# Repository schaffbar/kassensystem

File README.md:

# Kassensystem

## Projektbeschreibung

Dies ist die Geschichte für die Entwicklung eines Abrechnungssystems für die SchaffBar,
einer offenen Werkstatt. Es sollen die Anwesenheiten der Besucher als die Nutzungszeiten
für ausgewählte elektrische Geräte zu Abrechnungszwecken erfasst werden.

Mittels eines RFID-Tags, das dem Besucher ausgehändigt wird, bei der Registrierung an der Theke,
wird beim Betreten und Verlassen des Werkstattbereichs ein Zeitpaar bestimmt,
das zur Abrechnung im Kassensystem herangezogen wird.
An einem Gerät kann mittels des RFID-Tags und einem WLan-Relais die Versorgungsspannung
eines Gerätes ein und ausgeschlatet werden und damit ebenfalls ein weiteres Zeitpaar
erstellt werden, das zur Abrechnung verwendet werden kann.

Das Lesen der RFID-Tags kann mittels eines RFID-Lesers erfolgen,
während die Daten in einer Datenbank auf einem Server gespeichert werden.

Daraus ergibt sich für das System folgende Aufteilung
- rfidReader - Bereitstellung des RFID-Tags an unterschiedlichen Positionen
- Comm Edge Device (TimeMachine) - Software auf dem Server dient als Schnittstelle zum Datenbanksystem
- ein Kassensystem

Als Kassensystem wird aktuell mit einer Offline Version von Odoo gearbeitet,
diese läuft in einem Docker-Container, in einem weiteren Container befindet sich die Datenbank,
ein weiteren Container wird es für die TimeMachine-Software geben.

## rfidReader

An folgenden oben beschriebenen Position kann ein RFID-Reader zur Anwendung kommen.
- dem Tresen
- dem Eingangsbereich zur Werkstatt
- an einem elektrischem Gerät "Gerätekontrolle"
diese Anwendungsfälle werden im weiteren Verlauf auch UseCases genannt.

Aktuell wird die ArduinoIDE zur Entwicklung verwendet, um aber die verwendeten Bibliotheken mitzuliefern
soll die Entwicklung auf PlatformIO umgestellt werden.
Auch soll die LVGL Bibliothek zukünftig verwendet werden, damit später das Handling von Schaltflächen und
anderem leichter implementiert werden kann.

### Hardwarebeschreibung

Eine Mikroprozessorsystem soll folgende Hardwaremerkmale aufweisen.
- ein Mikroprozessor mit einer WLan-Schnittstelle zur Kommunikation mit dem Server und den Datenbanken,
- einem RFID-Modul zum Lesen der ID-Nummer
- ein Display zur Darstellung von Informationen an den Benutzer,
   beziehungsweise Interaktion über die Touch-Funktionalität.

### Softwarebeschreibung

### Konfigurationsdaten

Um den Konfigurationsaufwand gering zuhalten wird beim Start des RFID-Readers die MAC-Adresse an den Server gesendet,
und anhand der Einträge in der Datenbank werden die Konfigurationsdaten an den RFID-Reader übertragen.

#### Tresen

Nach dem Auflegen des RFID-Tags auf dem RFID-Reader wird diese an den Server übertragen und in einer Datensatz der Datenbank abgelegt und steht zur weiteren Verarbeitung am Tresen zur Verfügung, wie Bearbeitung der Besucherdaten, zur Abrechnung, oder ...
Am Tresen erfolgt die Zuordnung des RFID-Tags zu einem Besucher

#### Eingangsbereich

Durch die Registrierung des Besuchers an der Theke hat dieser einen RFID-Tag erhalten, im Anschluss kann er seine Sachen richten, die er mit in den Werkstattbereich nehmen möchte. Beim Betreten und Verlassen des Werkstattbereichs hält der Besucher sein RFID-Tag an den RFID-Leser zur Erstellung einer Zeitmarke, die Differenz der Zeitspanne entspricht der Nutzungsdauer zur Abrechung. In Abhängigkeit der vorhandenen Datenbankeinträge ergibt sich das Betreten bzw. Verlassen der Werkstatt. Zur Berücksichtigung von Pausen oder ähnlichem können in der Datenbank mehrere Zeitpaare
eines Besuchers angelegt werden.

#### Gerätekontrolle

In den Stammdaten eines Besuchers ist hinterlegt, ob für einen Kunden die jeweilige Unterweisung für das Gerät erfolgt ist,
damit kann die unberechtige Verwendung von Geräten verhindert und die Unfallgefahr reduziert werden.
Nur wenn die Unterweisung hinterlegt ist, darf die Versorgungsspannung eingeschaltet werden, auch hier erfolgt die Abfrage
über die die Software auf dem Server.

## Comm Edge Device --Namensfindung

Diese Software bildet das Bindeglied zwischen den RFID-Reader und der Datenbank,
in Abhängigkeit des UseCases und dem Ergebnis der Datenbankabfrage wird die entsprechende Ausgabe auf dem RFID-Reader gessteuert.

## Kassensystem-SW

Aktuell soll eine offline Version von Odoo als Kassensystem verwendet werden,
da hier viele Funktionen bereits vorhanden sind.
Die Kopplung der RFID-Reader an das Kassensystem sowie die Auswertung der zusätzlichen Informationen
aus den hinzugefügten Tabellen muss noch erfolgen.

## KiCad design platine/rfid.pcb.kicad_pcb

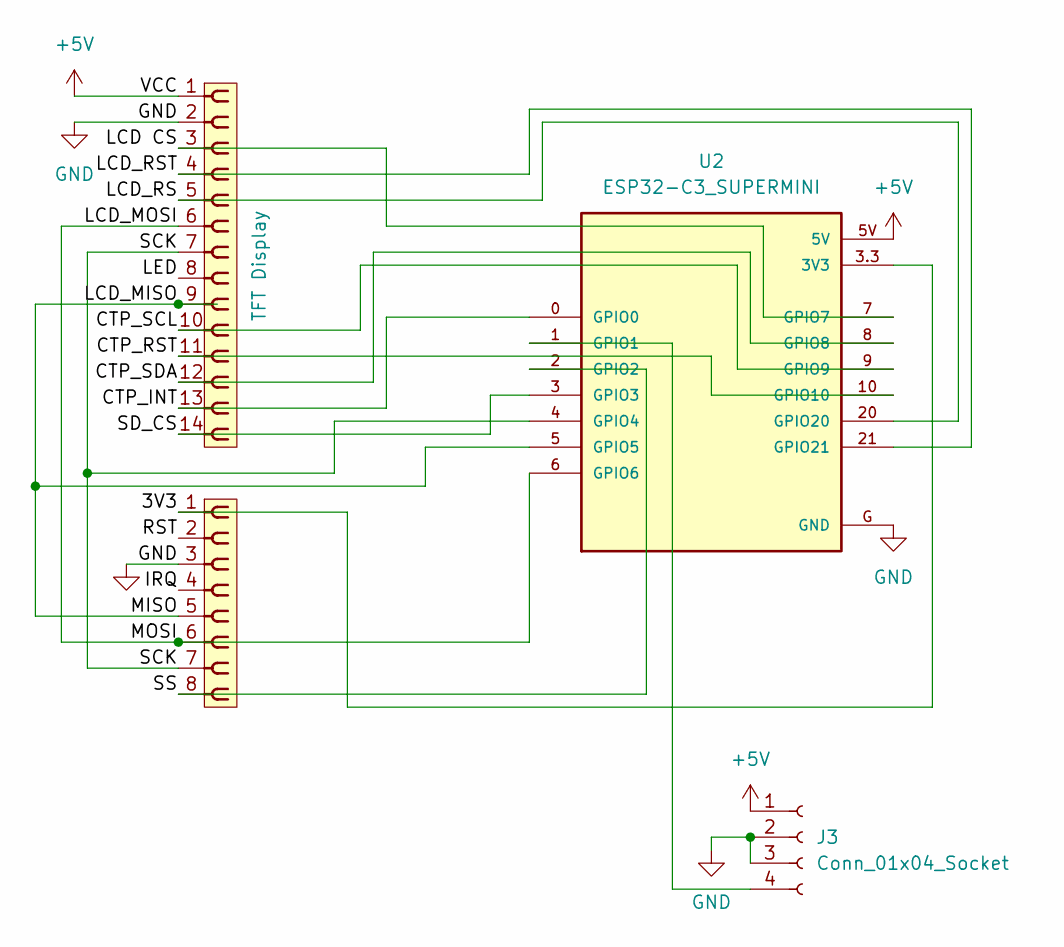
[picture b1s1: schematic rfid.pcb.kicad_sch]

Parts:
J1: TFT Display; PinSocket_1x14_P2.54mm_Vertical
J2: RFID Reader; PinSocket_1x08_P2.54mm_Vertical
J3: Conn_01x04_Socket; PinSocket_1x04_P2.54mm_Vertical
U2: ESP32-C3_SUPERMINI; MODULE_ESP32-C3_SUPERMINI

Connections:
+5V: J1.1, J3.1, U2.5V
/3V3: J2.1, U2.3.3 (3V3)
/CTP_INT: J1.13, U2.0 (GPIO0)
/CTP_RST: J1.11, U2.10 (GPIO10)
/CTP_SCL: J1.10, U2.9 (GPIO9)
/CTP_SDA: J1.12, U2.8 (GPIO8)
/IRQ: J2.4
/LCD CS: J1.3, U2.7 (GPIO7)
/LCD_MISO: J1.9, J2.5, U2.5 (GPIO5)
/LCD_MOSI: J1.6, J2.6, U2.6 (GPIO6)
/LCD_RS: J1.5, U2.20 (GPIO20)
/LCD_RST: J1.4, U2.21 (GPIO21)
/LED: J1.8
/RST: J2.2
/SCK: J1.7, J2.7, U2.4 (GPIO4)
/SD_CS: J1.14, U2.3 (GPIO3)
/SS: J2.8, U2.2 (GPIO2)
GND: J1.2, J2.3, J3.2, J3.3, U2.G (GND)
unnamed: J3.4, U2.1 (GPIO1)

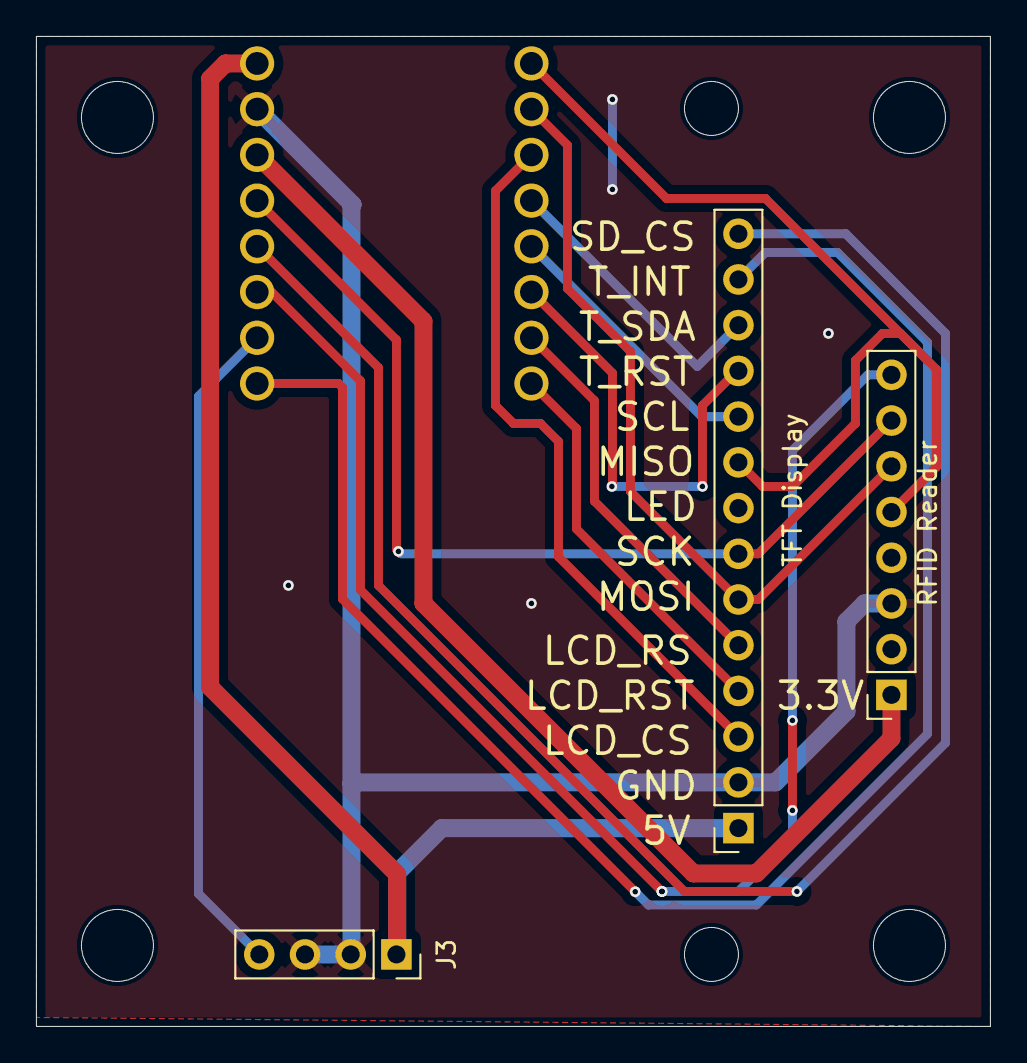
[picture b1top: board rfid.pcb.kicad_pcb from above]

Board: 2 copper layers, 53.0 x 55.0 mm, 4 parts (1 on the bottom side), 16 nets.

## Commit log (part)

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2025-03-24 Init
    Initialer Transfer der rfidReader Software
    hier fehlt noch der UseCase zum Schalten der Geräte und insgesamt ein intensiver Test
2025-03-24 update des Readme
2025-04-04 2. Version mit Löchern für das Display und GPIO1 nach SD_CS
2025-04-08 Update README.md
    fix bullet lists
2025-04-08 add readme
2025-04-20 added timemachine
2025-05-09 verwendete Bibliotheken für die Arduino IDE
    hier befinden sich alle verwendeten Bibliotheken mit ihren weiteren Abhängigkeiten
2025-05-24 added timemachine table prefix
2025-06-01 clipboard and checkout added
2025-06-01 fixed setting clipboard: upsert
2025-06-03 fix: correctly parse counter card requests
2025-06-04 create card if new card is presented to counter
2025-07-03 SoundAusgabe für Fehlermeldungen hinzugefügt + PinOut für BreadBoard angepasst
2025-07-17 ESP32 Update V0.3.1 UseCase AddTag hinzugefügt
2025-07-17 TimeMachine Update zu ESP32 ArduinoIDE V 0.3.1
2025-07-17 ArduinoIDE Library Update 07/2025
2025-07-18 ESP32 Update V0.3.2 UseCase AddTag Bildbewechsel im Idle State berichtigt
2025-07-19 ESP32 Update V0.3.3 Separierung der Zugangsdaten
2025-07-20 fix missing device
2025-07-20 fix missing sock
2025-07-20 autostart timemachine
2025-07-20 make timemachine available on lan
2025-07-20 refactored sockets to rest api
2025-07-23 initial commit for schaffbar-portal
2025-07-23 use latest angular version
2025-07-23 use latest angular material version
2025-07-28 implement basic interactions for tool object
2025-07-28 docu to understand python code
2025-07-30 implement basic interactions for rfid reader object
2025-07-30 refactoring of token assignment
2025-08-03 implement basic interactions for rfid tag
2025-08-03 add open questions to docu
2025-08-03 rename token package to token_assignment
2025-08-03 refactoring of customer package
2025-08-03 make intellij happy
2025-08-03 add tools section
2025-08-04 add use cases docu
2025-08-04 implement tool detail page
2025-08-06 ESP32 Update HTTP communication
2025-08-08 add rfid reader type property and add get rfid reader by mac address method
2025-08-08 fetch rfid tag by tag id
2025-08-08 extend arduino docu
2025-08-08 remove tag id property from rfid tag class
2025-08-08 ViewMapper should be package private
2025-08-08 rename token assignment to rfid tag assignment
2025-08-08 rename token to rfid tag assignment
2025-08-09 add rfid tag section
2025-08-09 random data for rfid tag
2025-08-09 add refresh button to rfid readers and tags list
2025-08-09 implement rfid tag assignment
2025-09-19 add build info goal to pom.xml
2025-09-19 add .env file to gitignore
2025-09-19 add Dockerfile
2025-09-19 thoughts on workshop usage
2025-09-20 multi stage build for backend
2025-09-20 add multi stage build for frontend
2025-09-20 add frontend to docker compose
2025-09-20 comment out delays in signal stores
2025-09-21 add deployment docu
2025-09-22 clean up logback file
2025-09-22 add .dockerignore file for backend
2025-09-22 copy lombok.config to build stage
2025-09-22 set active profile to prod in docker compose
2025-09-22 use single letters for RFID reader type
2025-09-22 add RFID reader id to tool class
2025-09-24 add assign RFID reader to tool method
2025-09-24 add assign RFID reader to tool use case
2025-09-26 configure environment specific api base url
2025-09-26 configure frontend environment
2025-09-26 remove default for FRONTEND_ENV in Dockerfile
2025-09-26 adapt .dockerignore file
2025-09-26 add defualts for backend und frontend env
2025-09-27 fix port
2025-10-01 remove dependency from backend
2025-10-01 add custom converter from string to customerId object
2025-10-05 add enter/exit workshop use case
2025-10-05 remove allowSignalWrites property in effect
2025-10-05 add open session tab in user detail page
2025-10-05 add todo list
2025-10-05 fix linter issues
2025-10-06 add unassign temporary RFID tag use case
2025-10-06 rename values of RfidReaderType and add key property
2025-10-06 more todos
2025-10-06 add @Transactional annotation to each use case
2025-10-07 add unassign RFID tag use case
2025-10-07 remove unassignmentDate property from RfidTagAssignment
2025-10-07 [frontend] implement unassign RFID tag use case
2025-10-08 add confirmation dialog before deleting user
2025-10-08 clean up communication with RFID reader
2025-10-08 move id value objects to id package
2025-10-08 move ValueObjectAssert to id package
2025-10-08 [frontend] add slidetoggle for member of an association
2025-10-09 fix NPE
2025-10-09 fix device controller
2025-10-18 set phone as optional
2025-10-18 adapt todos
2025-10-19 [frontend] remove standalone property
2025-10-19 [frontend] move user contact and address to new user-detail-info component
2025-10-19 [frontend] make user-address component editable depending on input parameter
2025-10-19 [frontend] implement update of user address
2025-10-20 [frontend] implement update of user contact
2025-10-21 rfidReader_UC_GateKeeperIn/Out
2025-10-21 rfidReader_UC_GateKeeperInOut
2025-10-23 [backend] add date of birth to customer
2025-10-23 [frontend] provide DatePipe for services
2025-10-23 [frontend] add date of birth to new customer form
2025-10-25 update angular
2025-10-25 [frontend] update angular material
2025-10-25 [frontend] update ngrx signal
2025-10-25 [frontend] show age group
2025-10-26 [backend] add interface to update customer name and date of birth
2025-10-26 adapt TODO's
2025-10-27 [backend] add interface to set and update club membership
2025-10-27 [frontend] set and update club membership
2025-11-03 [backend] add close workshop session implementation
2025-11-03 [backend] format code
2025-11-08 [backend] clean up
2025-11-08 [backend] add todo for close session use case
2025-11-08 [frontend] switch to active session interface
2025-11-08 [backend] remove unused interface
2025-11-13 [backend] implement error handling
2025-11-13 [frontend] exend budget
2025-11-13 [backend] fix user query
2025-12-09 server deployment
2025-12-18 Änderungen für Dietmar
2025-12-18 eclipse project files
2025-12-28 [frontend] fetch active session information when refresh user button clicked
2025-12-28 [backend] delete ide files
2025-12-28 [backend] revert .gitignore
2026-01-01 remove unused paramter
2026-01-02 add i18n for user detail
2026-01-03 add i18n for user open session
2026-01-03 add i18n for tools
2026-01-03 refac i18n
2026-01-03 add i18n for rfid tags
2026-01-05 [backend] revert last changes
2026-01-05 [backend] add todo for rest controllers
2026-01-05 [backend] move mapper to view/api model
2026-01-05 [backend] deliver units used for workshop session in rest controller
2026-01-05 [backend] fix total duration and used units calculation
2026-01-05 [frontend] add units used in open session page
2026-01-08 [frontend] remove public from .dockerignore
2026-01-08 [backend] set DEVUSECASE property properly
2026-01-23 [backend] switch to java 25
2026-02-07 CheckIn/Out ohne Units
2026-02-10 [backend] update RFID reader
2026-02-11 [frontend] add name property to RFID readers table
2026-02-11 [frontend] move rfid-reader-detail-info component to components
2026-02-11 [frontend] add rfid reader field to tool detail view
2026-02-15 [frontend] refactor tool detail page
2026-02-15 [backend] update tool info
2026-02-15 [frontend] update tool info
2026-02-15 [backend] implement rfid reader assignment to tool
2026-02-16 [frontend] make stores private
2026-02-16 [frontend] extract assigned rfid reader info to new component
2026-02-16 [backend] fix NullPointerException when assigning rfid reader to a tool
2026-02-16 [frontend] show only rfid readers of type switch box
2026-02-16 [frontend] mark already assigned rfid readers in combo box
2026-02-17 [backend] add clear RFID reader assignment interface to ToolController
2026-02-17 [frontend] add button to clear RFID reader assignment
2026-02-17 [frontend] add refresh button to all pages
2026-02-17 [frontend] change cursor in RFID tag list
2026-02-17 [frontend] add a confirmation dialog before deleting
2026-02-17 [frontend] add a confirmation dialog before clearing RFID reader assignment
2026-02-18 [frontend] move commands to model class
2026-02-18 [frontend] add new tool dialog
2026-02-18 [frontend] new tool dialog - load all rfid readers before opening dialog
2026-02-21 [backend] additional validation when creating a tool
2026-02-21 [frontend] new tool dialog - addtional validation
2026-02-21 [backend] add WLAN relais information to tool
2026-02-21 [frontend] add WLAN relais information to tool
2026-02-21 [frontend] add missing test files
2026-02-21 [frontend] validation of ip address
2026-02-21 [frontend] make derrived values more read-only style
2026-02-21 [frontend] clear ip address after setting type to undefined/null
2026-02-21 [frontend] use form to show WLAN relais information
2026-02-23 [frontend] update derived values when ip address has changed
2026-02-23 [frontend] fix editing of RFID reader type
2026-02-24 clean up TODOs
2026-02-24 [frontend] upgrade to angular 21
2026-02-24 [frontend] upgrade to angular material 21
2026-02-24 [frontend] upgrade to ngrx 21
2026-02-27 [backend] provide method to get all active workshop usages
2026-02-27 [backend] provide information about active users in workshop
2026-02-27 [frontend] add dashboard module with active users widget
2026-02-27 [frontend] transform widget to a dumb component
2026-02-27 [backend] add some data for dashboard
2026-03-17 [backend] implement tool usage tracking
2026-03-18 [backend] move all payloads to one package
2026-03-18 [backend] process messages coming from switch box
2026-03-20 [backend] provide information about tool usage
2026-03-20 [frontend] move user stores to shared folder
2026-03-20 [frontend] show tool usage in user details page
2026-03-20 [frontend] improve styling
2026-04-18 update TODO
2026-04-18 [backend] add new interface to change RFID reader type
2026-04-18 [backend] add request param rfidReaderId to getAllTools interface
2026-04-18 [frontend] add button for changing of rfid reader type
2026-04-18 [backend] add validation when changing type from switch box to other type
2026-04-18 [backend] adapt tool dashboard path
2026-04-18 [frontend] add active tools to dashboard
2026-04-18 [backend] optimize imports and format code
2026-05-04 [backend] add patch to allowed methods
2026-05-04 [backend] remove type from update request body
2026-05-11 [backend] add relay info for init call
2026-05-11 [backend] replace placeholder with ip address
2026-05-11 [backend] fix init response
2026-05-15 [backend] move aggregate documentation to aggregate package
2026-05-15 [backend] add skill for creating a domain/aggregate object
2026-05-15 [backend] add tool certificate domain object
2026-05-16 [backend] implement delete tool certification
2026-05-18 [frontend] delete all tests
2026-05-18 [backend] turn on tool only if active tool certification is present
2026-05-18 [backend] improve error message
2026-05-18 [frontend] clean up create tool dialog
2026-05-25 [backend] add and remove instructors for a tool
2026-05-25 [backend] cleanup - delete WithEvents objects
2026-05-27 [backend] refactoring of tool package
2026-05-27 [backend] tool - add api
2026-05-27 [frontend] add and remove intructors for a tool
2026-05-30 [frontend] restructure tool detail page
2026-05-30 [backend] tool - reorder tool api
2026-05-31 [backend] new tool properties - tool area and certification requirement
2026-05-31 [frontend] new tool properties - tool area and certification requirement
2026-05-31 [backend] fix tool deletion
2026-05-31 [backend] merge dashboard packages (tool_dashboard, workshop_dashboard) into one dashboard package
2026-05-31 [backend] remove foreign key
2026-05-31 [backend] cleanup ToolEventPayload class
2026-06-04 [backend] refactoring of customer package
2026-06-04 [backend] refactoring of rfid_reader package
